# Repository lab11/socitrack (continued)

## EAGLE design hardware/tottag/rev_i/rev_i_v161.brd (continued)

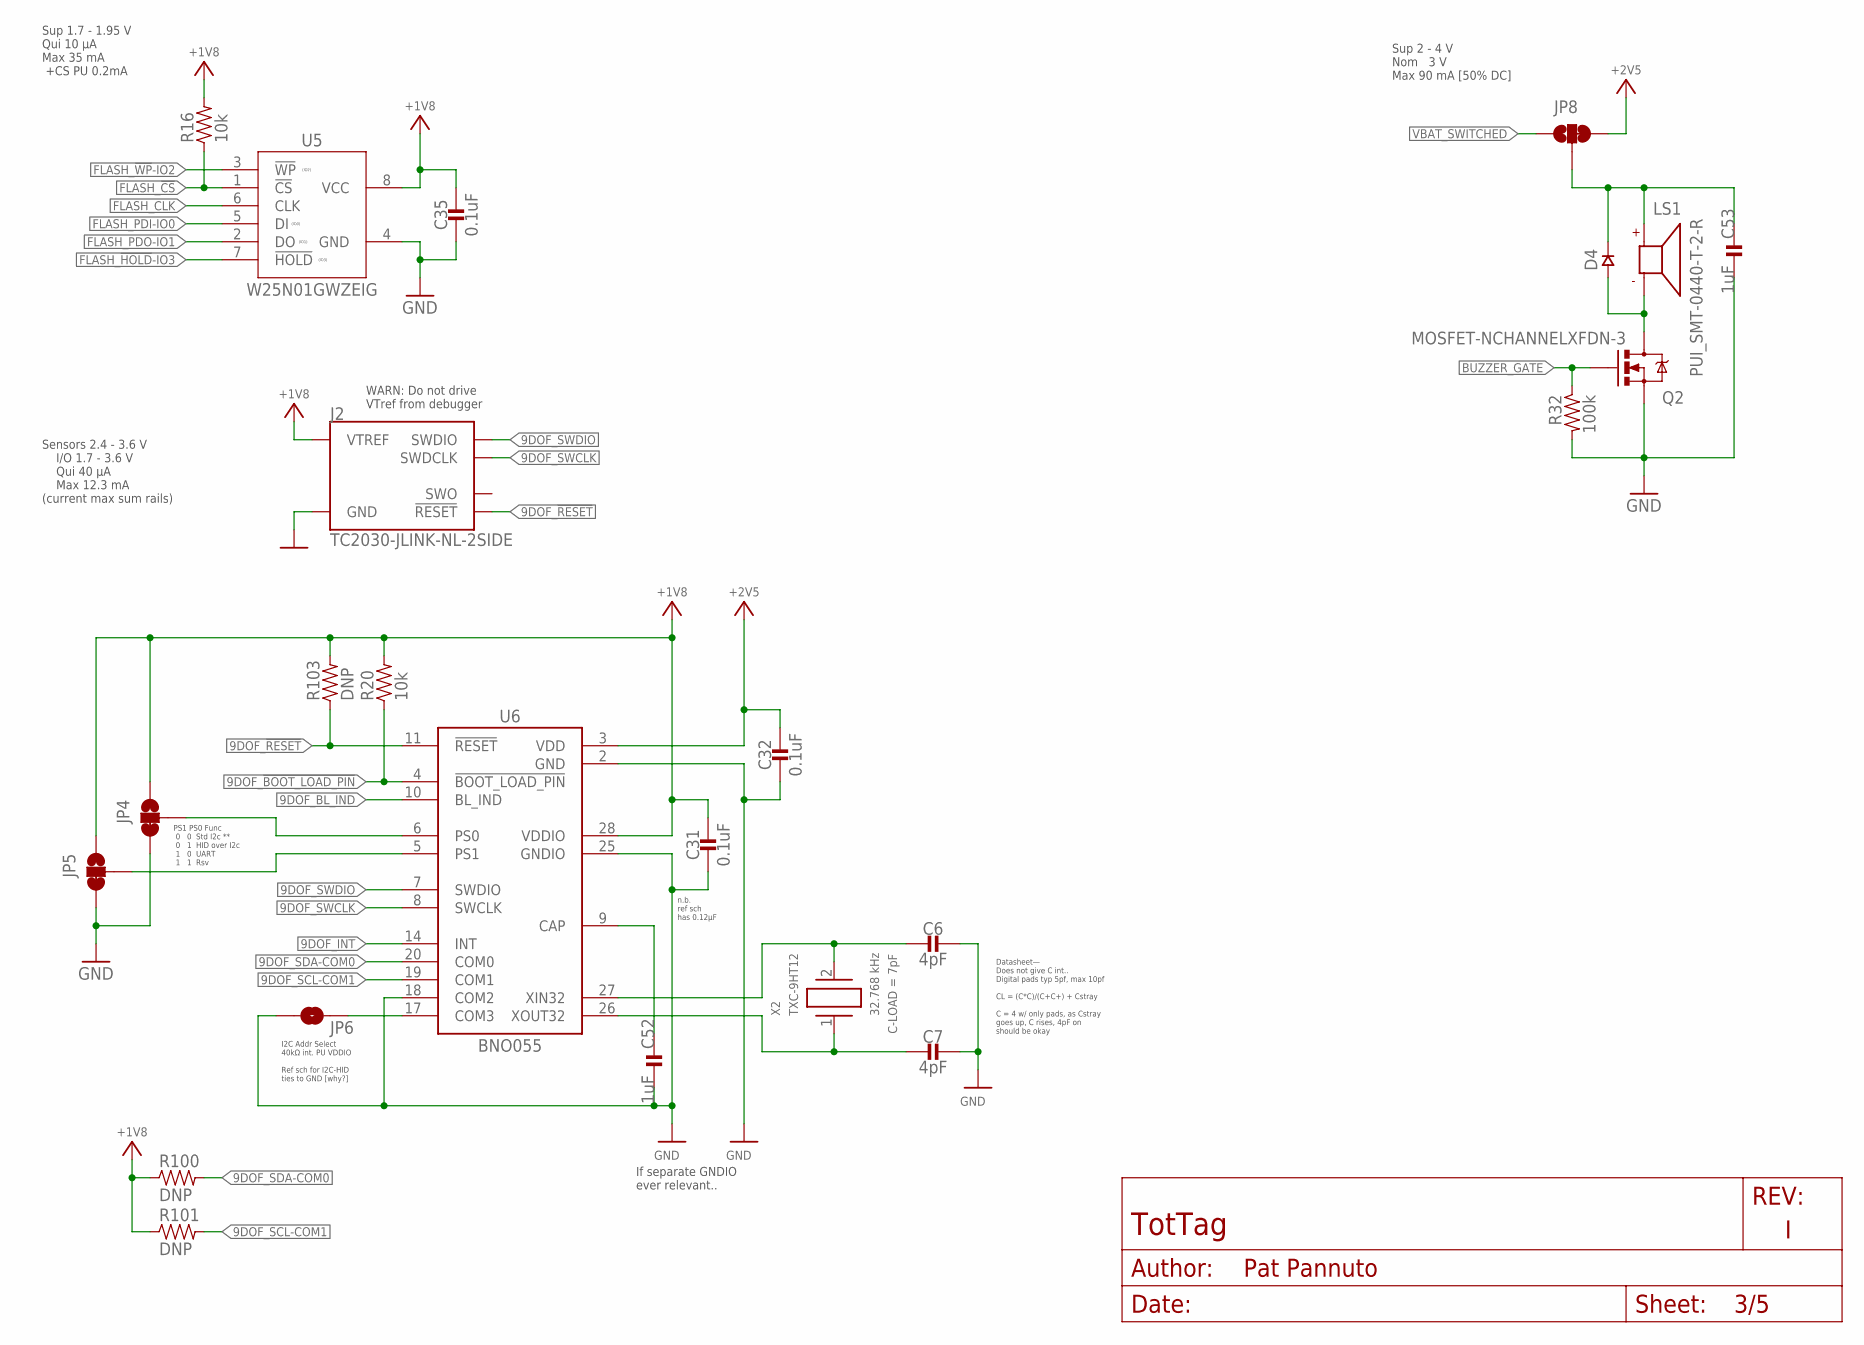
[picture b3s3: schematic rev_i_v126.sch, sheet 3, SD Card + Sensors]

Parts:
C6, C7: 4pF; 0201_CAP; MPN GRM0335C1H4R0BA01D
C31, C32, C35: 0.1uF; 0402_CAP; MPN CL05A104KP5NNNC
C52, C53: 1uF; 0201_CAP; MPN GRM033R61A105ME44D
D4: DIODE0402; 0402_DIODE; MPN CDSQR400B-HF; DIGIKEY 641-2087-1-ND
J2: TC2030-JLINK-NL-2SIDE; TC2030-IDC-NL-2SIDE
JP4, JP5, JP8: JUMPER-SMT_3_1-NC_TRACE_SILK; SMT-JUMPER_3_1-NC_TRACE_SILK
JP6: JUMPER-SMT_2_NO_SILK; SMT-JUMPER_2_NO_SILK
LS1: PUI_SMT-0440-T-2-R; SMT-0440-T-2-R
Q2: MOSFET-NCHANNELXFDN-3; XFDFN-3
R16, R20: 10k; 0402_RES; MPN RC0402JR-0710KL; DIGIKEY 311-10KJRCT-ND
R32: 100k; 0402_RES; MPN RT0402BRE07100KL
R100, R101, R103: DNP; 0603-RES
U5: W25N01GWZEIG; WSON127P800X600X80-9T430X340N
U6: BNO055; LGA28R0P510X4_5P2X3P8X1
X2: TXC-9HT12; MPN 9HT12-32.768KDZY-T

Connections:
9DOF_!BOOT_LOAD_PIN: R20.1, U6.4 (!BOOT_LOAD_PIN); also elsewhere on the board
9DOF_!RESET: J2.3 (!RESET), J2.B3 (!RESET), R103.1, U6.11 (!RESET); also elsewhere on the board
9DOF_BL_IND: U6.10 (BL_IND); also elsewhere on the board
9DOF_CAP: C52.P$1 (1), U6.9 (CAP)
9DOF_INT: U6.14 (INT); also elsewhere on the board
9DOF_SCL-COM1: R101.2, U6.19 (COM1); also elsewhere on the board
9DOF_SDA-COM0: R100.2, U6.20 (COM0); also elsewhere on the board
9DOF_SWCLK: J2.4 (SWDCLK), J2.B4 (SWDCLK), U6.8 (SWCLK)
9DOF_SWDIO: J2.2 (SWDIO), J2.B2 (SWDIO), U6.7 (SWDIO)
9DOF_XI: C6.P$2 (2), U6.27 (XIN32), X2.2
9DOF_XO: C7.P$2 (2), U6.26 (XOUT32), X2.1
+1V8: C31.1, C35.1, J2.1 (VTREF), J2.B1 (VTREF), JP4.1, JP5.1, R16.2, R20.2, R100.1, R101.1, R103.2, U5.8 (VCC), U6.28 (VDDIO); also elsewhere on the board
+2V5: C32.1, JP8.3, U6.3 (VDD); also elsewhere on the board
BUZZER_GATE: Q2.G, R32.1; also elsewhere on the board
BUZZER_SUPPLY: C53.P$1 (1), D4.CATHODE, JP8.2, LS1.+
FLASH_!CS: R16.1, U5.1 (!CS); also elsewhere on the board
FLASH_!HOLD!-IO3: U5.7 (!HOLD); also elsewhere on the board
FLASH_!WP!-IO2: U5.3 (!WP); also elsewhere on the board
FLASH_CLK: U5.6 (CLK); also elsewhere on the board
FLASH_PDI-IO0: U5.5 (DI); also elsewhere on the board
FLASH_PDO-IO1: U5.2 (DO); also elsewhere on the board
GND: C6.P$1 (1), C7.P$1 (1), C31.2, C32.2, C35.2, C52.P$2 (2), C53.P$2 (2), J2.5 (GND), J2.B5 (GND), JP4.3, JP5.3, JP6.1, Q2.S, R32.2, U5.4 (GND), U6.2 (GND), U6.18 (COM2), U6.25 (GNDIO); also elsewhere on the board
unnamed: D4.ANODE, LS1.- (N), Q2.D
unnamed: JP4.2, U6.6 (PS0)
unnamed: JP5.2, U6.5 (PS1)
unnamed: JP6.2, U6.17 (COM3)
VBAT_SWITCHED: JP8.1; also elsewhere on the board

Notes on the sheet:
Sup 1.7 - 1.95 V Qui 10 µA Max 35 mA +CS PU 0.2mA
Sensors 2.4 - 3.6 V I/O 1.7 - 3.6 V Qui 40 µA Max 12.3 mA (current max sum rails)
Sup 2 - 4 V Nom 3 V Max 90 mA [50% DC]
PS1 PS0 Func 0 0 Std I2c ** 0 1 HID over I2c 1 0 UART 1 1 Rsv
If separate GNDIO ever relevant..
I2C Addr Select 40kΩ int. PU VDDIO Ref sch for I2C-HID ties to GND [why?]
n.b. ref sch has 0.12µF
WARN: Do not drive VTref from debugger
Datasheet— Does not give C int.. Digital pads typ 5pf, max 10pf CL = (C*C)/(C+C+) + Cstray C = 4 w/ only pads, as Cstray goes up, C rises, 4pF on should be okay

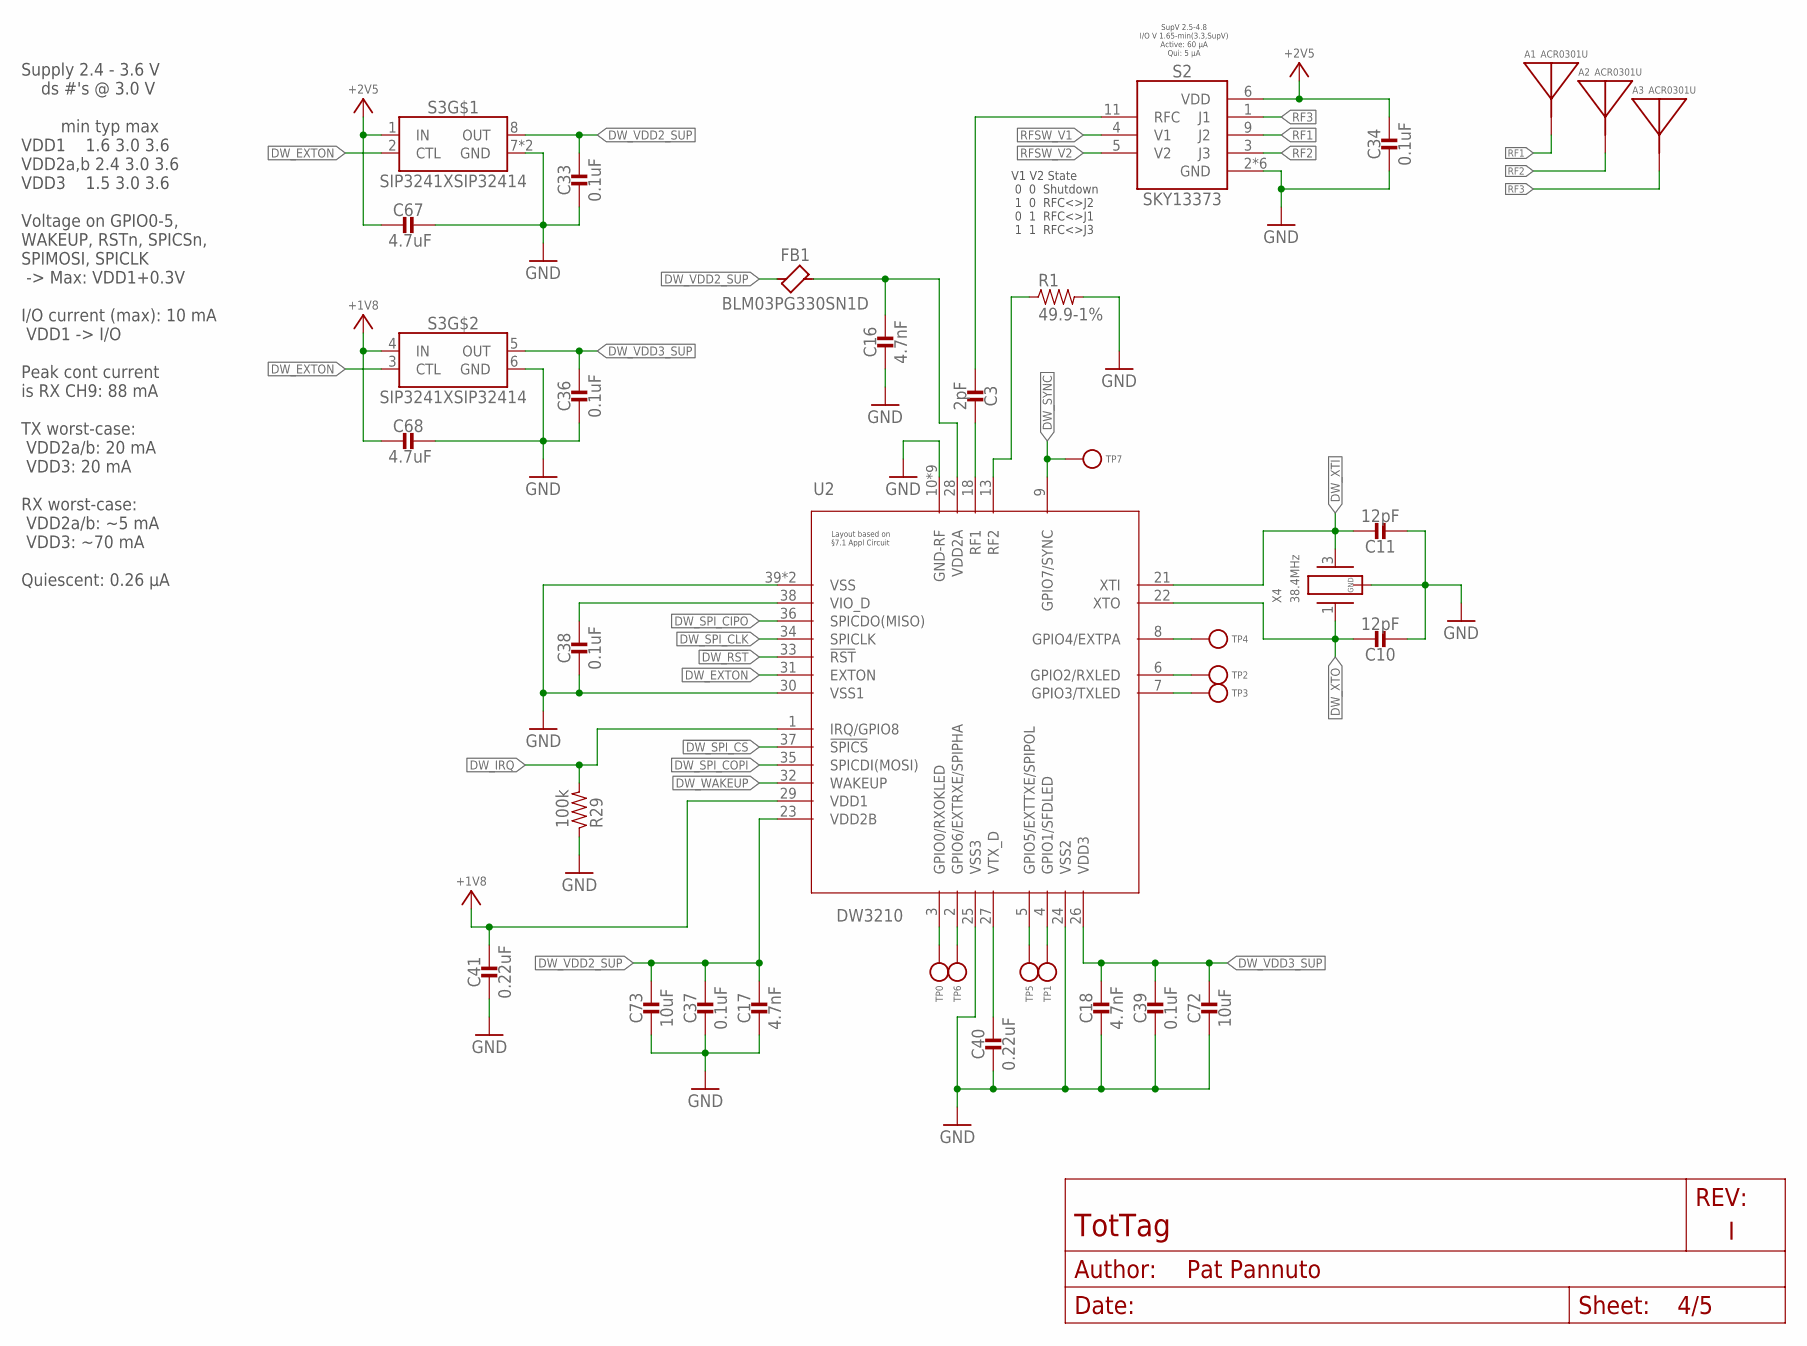
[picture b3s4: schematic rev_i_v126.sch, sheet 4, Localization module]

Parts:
A1, A2, A3: ACR0301U
C3: 2pF; 0201_CAP; MPN CBR02C209A5GAC
C10, C11: 12pF; 0402_CAP; MPN CBR04C120F5GAC; DIGIKEY 399-8815-2-ND
C16, C17, C18: 4.7nF; 0402_CAP; MPN C0402C472K3RAC7867
C33, C34, C36, C37, C38, C39: 0.1uF; 0402_CAP; MPN CL05A104KP5NNNC
C40, C41: 0.22uF; 0402_CAP; MPN CL05A224KP5NNNC
C67, C68: 4.7uF; 0402_CAP; MPN CL05A475MP5NRNC
C72, C73: 10uF; 0603_CAP; MPN CM105X5R106M25AT; DIGIKEY 1253-CM105X5R106M25ATCT-ND
FB1: BLM03PG330SN1D; 0201_FB; MPN BLM03PG330SN1D
R1: 49.9-1%; 0201_RES; MPN ERJ-1GNF49R9C
R29: 100k; 0402_RES; MPN RT0402BRE07100KL
S2: SKY13373
S3: SIP3241XSIP32414; TDFN2X2X0P6-8
TP0, TP1, TP2, TP3, TP4, TP5, TP6, TP7: TEST-POINT; PAD.03X.03
U2: DW3210; QFN40P500X500X80-40N
X4: 38.4MHz; FA-20H; MPN FA-20H 38.4000MF10Z-AS3; DIGIKEY SER3631CT-ND

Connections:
!DW_RST: U2.33 (!RST); also elsewhere on the board
!DW_SPI_CS: U2.37 (!SPICS); also elsewhere on the board
+1V8: C41.1, C68.2, S3.4 (IN), U2.29 (VDD1); also elsewhere on the board
+2V5: C34.1, C67.2, S2.6 (VDD), S3.1 (IN); also elsewhere on the board
DW_EXTON: S3.2 (CTL), S3.3 (CTL), U2.31 (EXTON)
DW_GPIO4: TP4.P$1, U2.8 (GPIO4/EXTPA)
DW_GPIO5: TP5.P$1, U2.5 (GPIO5/EXTTXE/SPIPOL)
DW_GPIO6: TP6.P$1, U2.2 (GPIO6/EXTRXE/SPIPHA)
DW_IRQ: R29.2, U2.1 (IRQ/GPIO8); also elsewhere on the board
DW_RF1: C3.P$1 (1), U2.18 (RF1)
DW_RF2: R1.1, U2.13 (RF2)
DW_RXLED: TP2.P$1, U2.6 (GPIO2/RXLED)
DW_RXOKLED: TP0.P$1, U2.3 (GPIO0/RXOKLED)
DW_SFDLED: TP1.P$1, U2.4 (GPIO1/SFDLED)
DW_SPI_CIPO: U2.36 (SPICDO(MISO)); also elsewhere on the board
DW_SPI_CLK: U2.34 (SPICLK); also elsewhere on the board
DW_SPI_COPI: U2.35 (SPICDI(MOSI)); also elsewhere on the board
DW_SYNC: TP7.P$1, U2.9 (GPIO7/SYNC)
DW_TXLED: TP3.P$1, U2.7 (GPIO3/TXLED)
DW_VDD2A: C16.1, FB1.P$2, U2.28 (VDD2A)
DW_VDD2_SUP: C17.1, C33.1, C37.1, C73.1, FB1.P$1, S3.8 (OUT), U2.23 (VDD2B)
DW_VDD3_SUP: C18.1, C36.1, C39.1, C72.1, S3.5 (OUT), U2.26 (VDD3)
DW_VIO_D: C38.1, U2.38 (VIO_D)
DW_VTX_D: C40.1, U2.27 (VTX_D)
DW_WAKEUP: U2.32 (WAKEUP); also elsewhere on the board
DW_XTI: C11.1, U2.21 (XTI), X4.3 (2)
DW_XTO: C10.1, U2.22 (XTO), X4.1
GND: C10.2, C11.2, C16.2, C17.2, C18.2, C33.2, C34.2, C36.2, C37.2, C38.2, C39.2, C40.2, C41.2, C67.1, C68.1, C72.2, C73.2, R1.2, R29.1, S2.2 (GND), S2.7 (GND), S2.8 (GND), S2.10 (GND), S2.12 (GND), S2.PAD (GND), S3.6 (GND), S3.7 (GND), S3.PAD (GND), U2.10 (GND-RF), U2.11 (GND-RF), U2.12 (GND-RF), U2.14 (GND-RF), U2.15 (GND-RF), U2.16 (GND-RF), U2.17 (GND-RF), U2.19 (GND-RF), U2.20 (GND-RF), U2.24 (VSS2), U2.25 (VSS3), U2.30 (VSS1), U2.39 (VSS), U2.40 (VSS), X4.2 (GND), X4.4 (GND); also elsewhere on the board
RF1: A1.FEED, S2.9 (J2)
RF2: A2.FEED, S2.3 (J3)
RF3: A3.FEED, S2.1 (J1)
RFC: C3.P$2 (2), S2.11 (RFC)
RFSW_V1: S2.4 (V1); also elsewhere on the board
RFSW_V2: S2.5 (V2); also elsewhere on the board

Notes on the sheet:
Supply 2.4 - 3.6 V ds #'s @ 3.0 V min typ max VDD1 1.6 3.0 3.6 VDD2a,b 2.4 3.0 3.6 VDD3 1.5 3.0 3.6 Voltage on GPIO0-5, WAKEUP, RSTn, SPICSn, SPIMOSI, SPICLK -> Max: VDD1+0.3V I/O current (max): 10 mA VDD1 -> I/O Peak cont current is RX CH9: 88 mA TX worst-case: VDD2a/b: 20 mA VDD3: 20 mA RX worst-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
SupV 2.5-4.8 I/O V 1.65-min(3.3,SupV) Active: 60 µA Qui: 5 µA
V1 V2 State 0 0 Shutdown 1 0 RFC<>J2 0 1 RFC<>J1 1 1 RFC<>J3

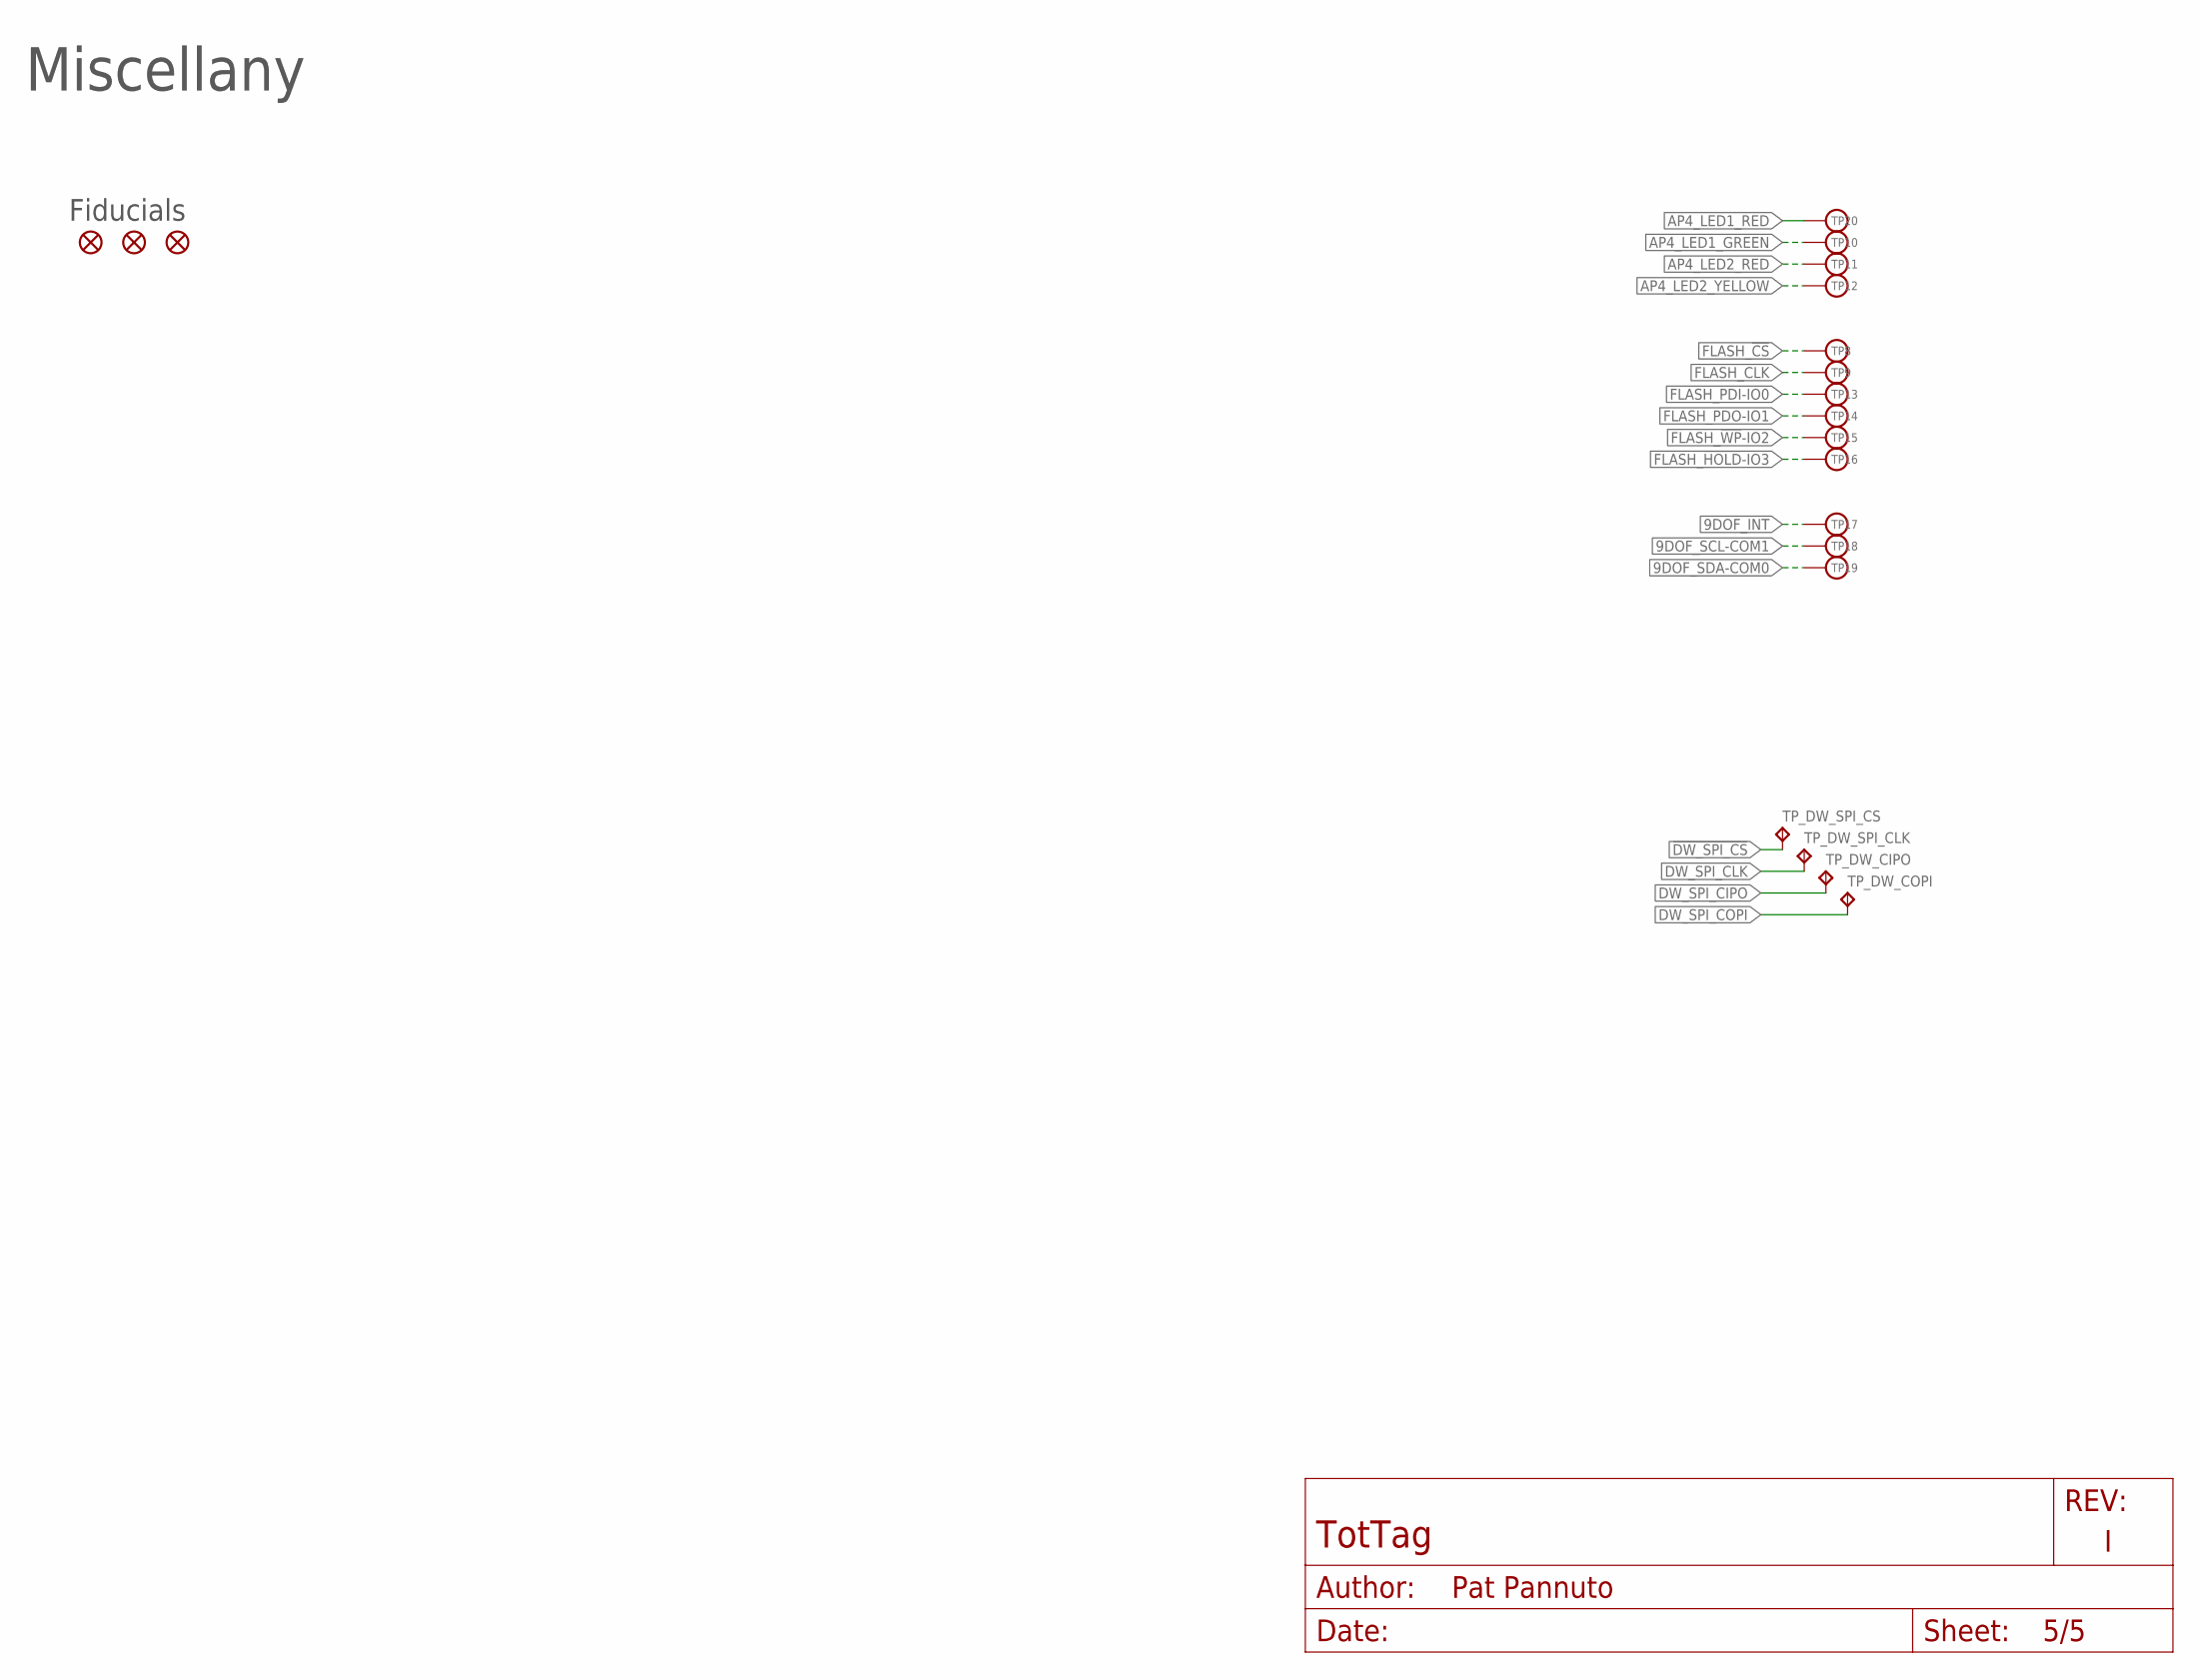
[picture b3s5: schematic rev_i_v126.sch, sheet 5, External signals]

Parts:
FD1, FD2, FD3: FIDUCIAL1X2; FIDUCIAL-1X2
TP8, TP9, TP10, TP11, TP12, TP13, TP14, TP15, TP16, TP17, TP18, TP19, TP20: TEST-POINT; PAD.03X.03
TP_DW_CIPO: TPTP06SQ; TP06SQ
TP_DW_COPI: TPTP06SQ; TP06SQ
TP_DW_SPI_CLK: TPTP06SQ; TP06SQ
TP_DW_SPI_CS: TPTP06SQ; TP06SQ

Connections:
9DOF_INT: TP17.P$1; also elsewhere on the board
9DOF_SCL-COM1: TP18.P$1; also elsewhere on the board
9DOF_SDA-COM0: TP19.P$1; also elsewhere on the board
!DW_SPI_CS: TP_DW_SPI_CS.TP; also elsewhere on the board
AP4_LED1_GREEN: TP10.P$1; also elsewhere on the board
AP4_LED1_RED: TP20.P$1; also elsewhere on the board
AP4_LED2_RED: TP11.P$1; also elsewhere on the board
AP4_LED2_YELLOW: TP12.P$1; also elsewhere on the board
DW_SPI_CIPO: TP_DW_CIPO.TP; also elsewhere on the board
DW_SPI_CLK: TP_DW_SPI_CLK.TP; also elsewhere on the board
DW_SPI_COPI: TP_DW_COPI.TP; also elsewhere on the board
FLASH_!CS: TP8.P$1; also elsewhere on the board
FLASH_!HOLD!-IO3: TP16.P$1; also elsewhere on the board
FLASH_!WP!-IO2: TP15.P$1; also elsewhere on the board
FLASH_CLK: TP9.P$1; also elsewhere on the board
FLASH_PDI-IO0: TP13.P$1; also elsewhere on the board
FLASH_PDO-IO1: TP14.P$1; also elsewhere on the board

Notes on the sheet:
Miscellany
Fiducials

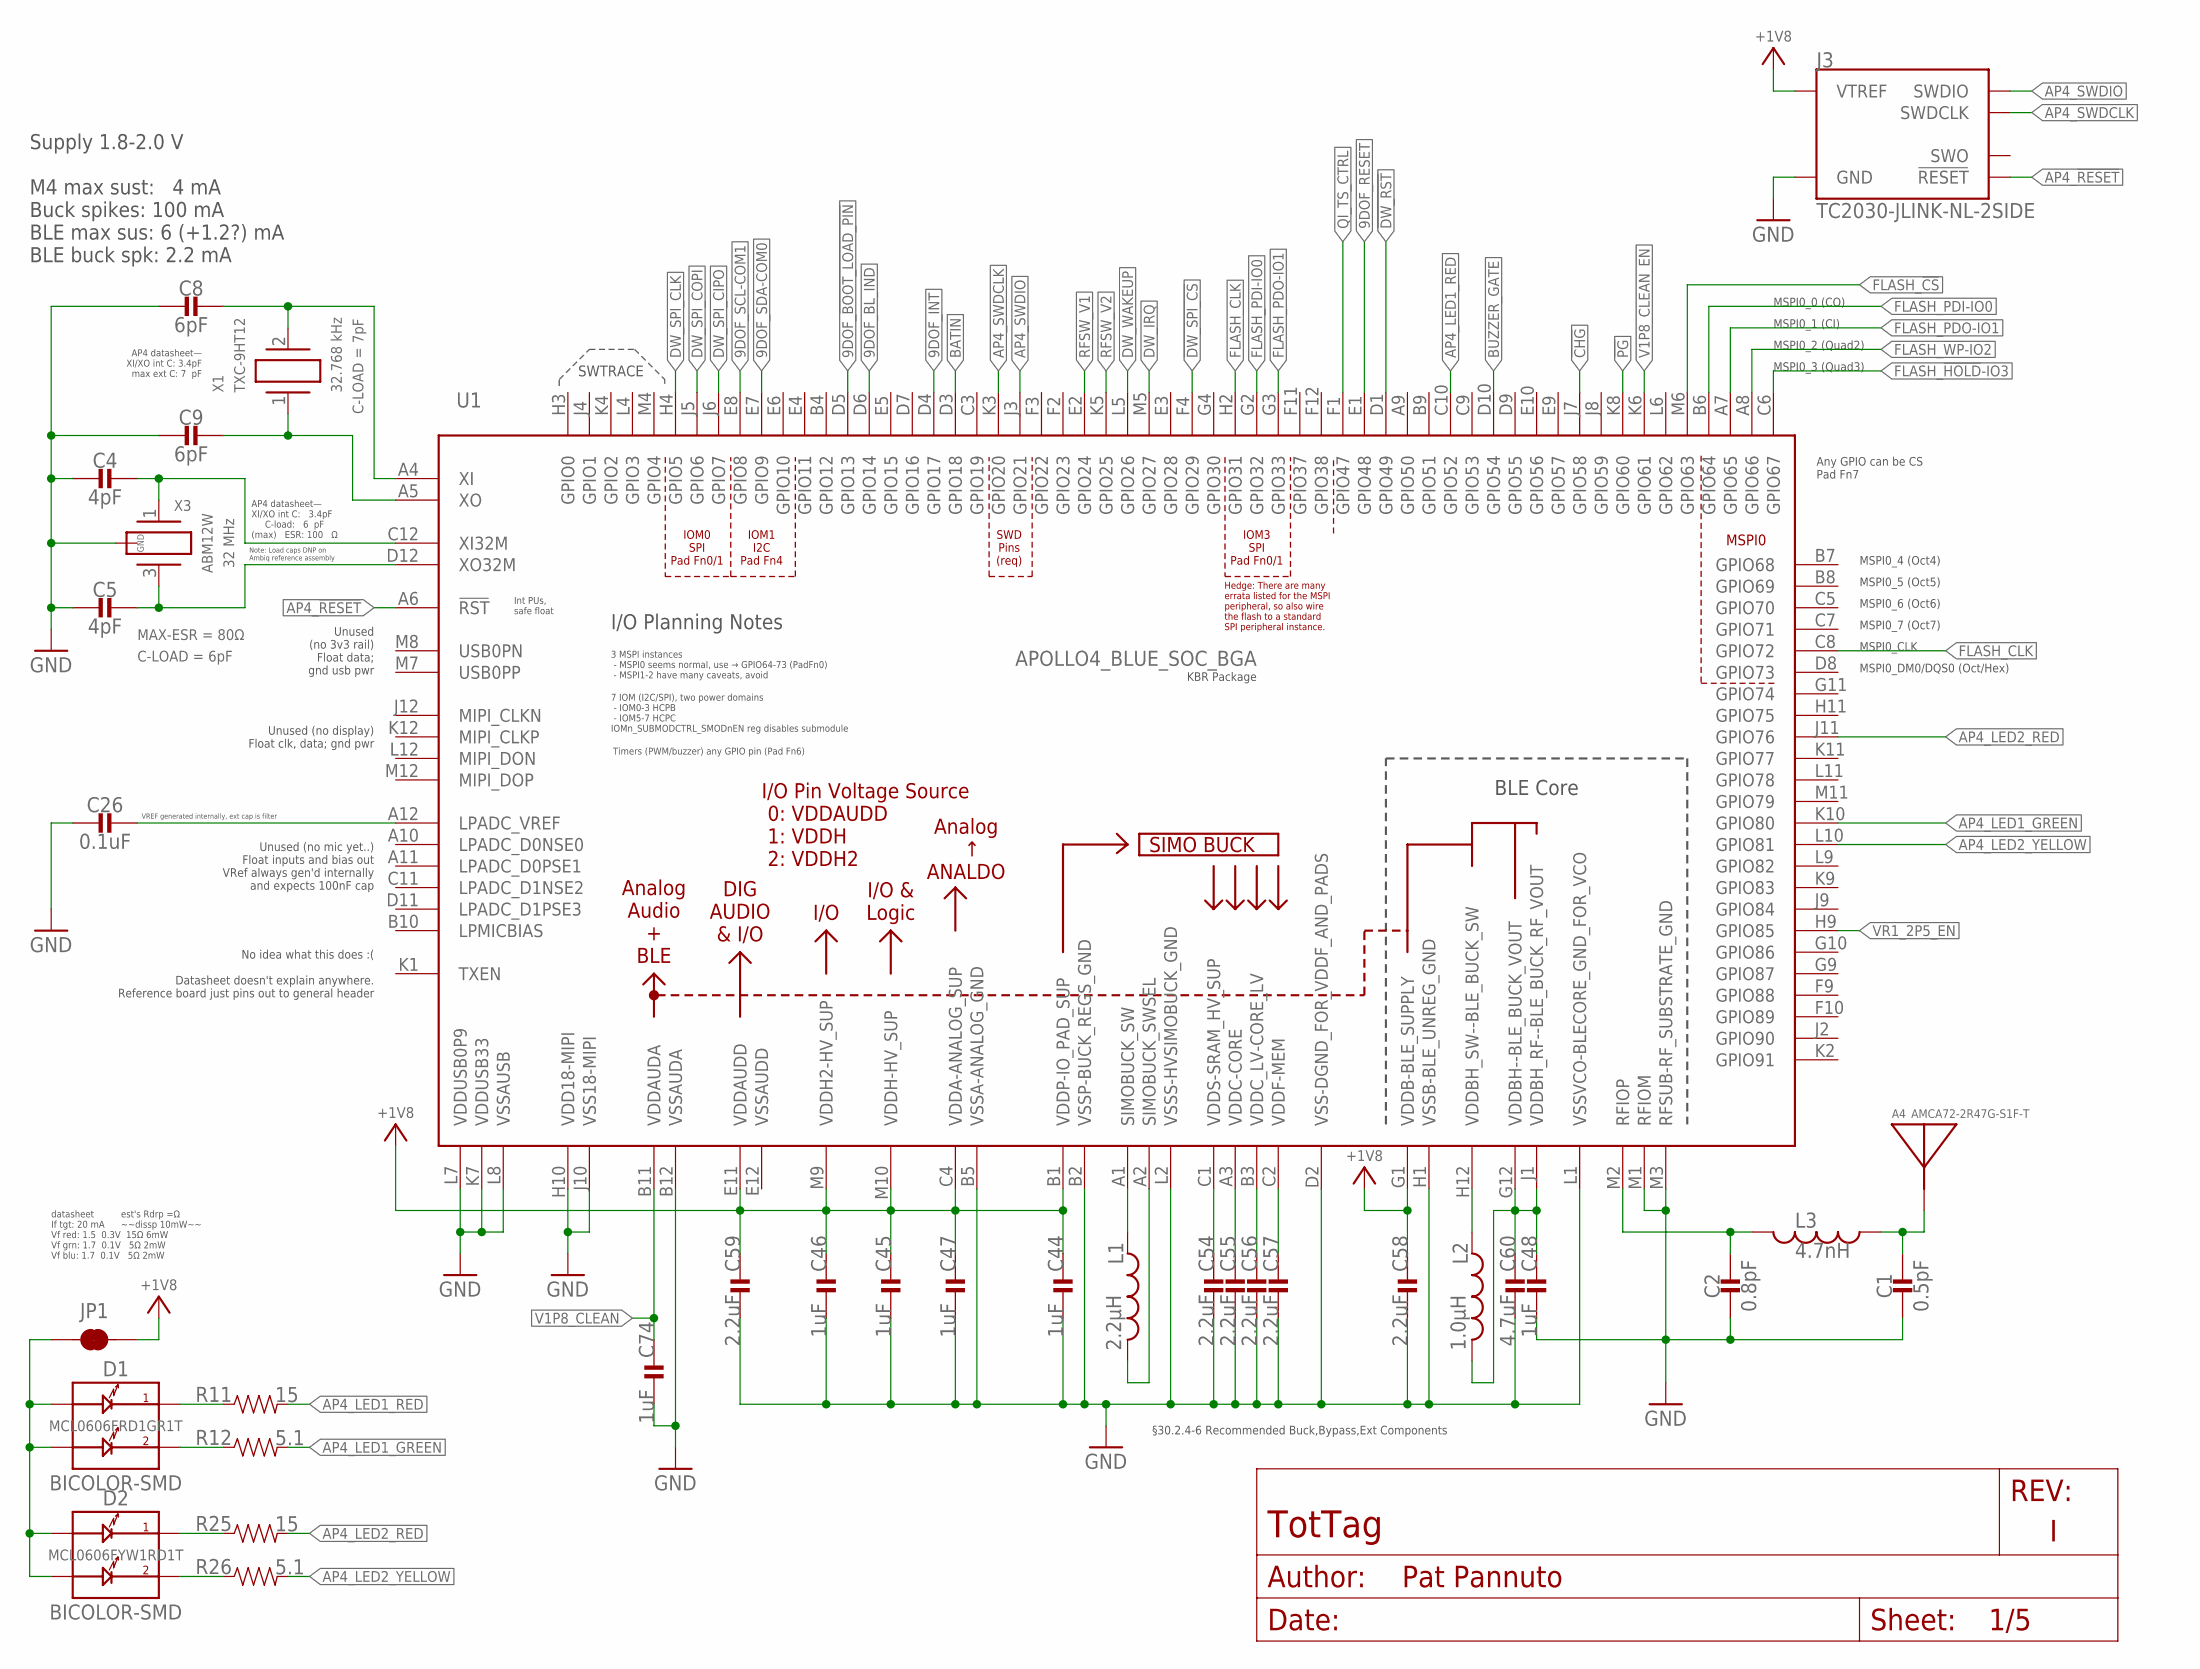
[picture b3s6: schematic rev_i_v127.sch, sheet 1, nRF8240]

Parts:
A4: AMCA72-2R47G-S1F-T; AMCA72-2R470G-S1F-T
C1: 0.5pF; 0402_CAP; MPN GJM1555C1HR50WB01D
C2: 0.8pF; 0402_CAP; MPN GJM1555C1HR80WB01D
C4, C5: 4pF; 0201_CAP; MPN GRM0335C1H4R0BA01D
C8, C9: 6pF; 0201_CAP; MPN GRM0335C1H6R0BA01D
C26: 0.1uF; 0201_CAP; MPN CL05A104KP5NNNC
C44, C45, C46, C47, C48, C74: 1uF; 0201_CAP; MPN GRM033R61A105ME44D
C54, C55, C56, C57, C58, C59: 2.2uF; 0201_CAP; MPN GRM033R61A225KE47D
C60: 4.7uF; 0402_CAP; MPN CL05A475MP5NRNC
D1: BICOLOR-SMD; LED-0606; MPN MCL0606FRD1GR1T
D2: BICOLOR-SMD; LED-0606; MPN MCL0606FYW1RD1T
J3: TC2030-JLINK-NL-2SIDE; TC2030-IDC-NL-2SIDE
JP1: JUMPER-SMT_2_NC_TRACE_SILK; SMT-JUMPER_2_NC_TRACE_SILK
L1: 2.2µH; 0805_CAP; MPN DFE201210U-2R2M=P2
L2: 1.0µH; 0603_CAP; MPN DFE18SAN1R0ME0L
L3: 4.7nH; 0402_CAP; MPN LQW15AN4N7G8ZD
R11, R25: 15; 0402_RES; MPN RC0402JR-0715RL
R12, R26: 5.1; 0402_RES; MPN RC0402JR-075R1L
U1: APOLLO4_BLUE_SOC_BGA
X1: TXC-9HT12; MPN 9HT12-32.768KDZY-T
X3: ABM12W; MPN ABM12W-32.0000MHZ-6-D1X-T3

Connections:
9DOF_!BOOT_LOAD_PIN: U1.D5 (GPIO13); also elsewhere on the board
9DOF_!RESET: U1.E1 (GPIO48); also elsewhere on the board
9DOF_BL_IND: U1.D6 (GPIO14); also elsewhere on the board
9DOF_INT: U1.D4 (GPIO17); also elsewhere on the board
9DOF_SCL-COM1: U1.E8 (GPIO8); also elsewhere on the board
9DOF_SDA-COM0: U1.E7 (GPIO9); also elsewhere on the board
!CHG: U1.J7 (GPIO58); also elsewhere on the board
!DW_RST: U1.D1 (GPIO49); also elsewhere on the board
!DW_SPI_CS: U1.F4 (GPIO29); also elsewhere on the board
!PG: U1.K8 (GPIO60); also elsewhere on the board
+1V8: C44.P$1 (1), C45.P$1 (1), C46.P$1 (1), C47.P$1 (1), C58.P$1 (1), C59.P$1 (1), J3.1 (VTREF), J3.B1 (VTREF), JP1.2, U1.B1 (VDDP-IO_PAD_SUP), U1.C4 (VDDA-ANALOG_SUP), U1.E11 (VDDAUDD), U1.G1 (VDDB-BLE_SUPPLY), U1.M9 (VDDH2-HV_SUP), U1.M10 (VDDH-HV_SUP); also elsewhere on the board
AP4_!RESET: J3.3 (!RESET), J3.B3 (!RESET), U1.A6 (!RST)
AP4_LED1_GREEN: R12.2, U1.K10 (GPIO80); also elsewhere on the board
AP4_LED1_RED: R11.2, U1.C10 (GPIO52); also elsewhere on the board
AP4_LED2_BLUE_COMM: D1.1-C1 (C1), R11.1
AP4_LED2_RED: R25.2, U1.J11 (GPIO76); also elsewhere on the board
AP4_LED2_YELLOW: R26.2, U1.L10 (GPIO81); also elsewhere on the board
AP4_LED_BLUE_COMM: D2.2-C2 (C2), R26.1
AP4_LED_GREEN_COMM: D2.1-C1 (C1), R25.1
AP4_LED_RED_COMM: D1.2-C2 (C2), R12.1
AP4_LPADC_VREF: C26.P$1 (1), U1.A12 (LPADC_VREF)
AP4_RFIOP: C2.1, L3.2, U1.M2 (RFIOP)
AP4_SWDCLK: J3.4 (SWDCLK), J3.B4 (SWDCLK), U1.K3 (GPIO20)
AP4_SWDIO: J3.2 (SWDIO), J3.B2 (SWDIO), U1.J3 (GPIO21)
AP4_VDDBH: C48.P$1 (1), C60.1, L2.2, U1.G12 (VDDBH--BLE_BUCK_VOUT), U1.J1 (VDDBH_RF--BLE_BUCK_RF_VOUT)
AP4_VDDBH_SW: L2.1, U1.H12 (VDDBH_SW--BLE_BUCK_SW)
AP4_VDDC: C55.P$1 (1), U1.A3 (VDDC-CORE)
AP4_VDDC_LV: C56.P$1 (1), U1.B3 (VDDC_LV-CORE_LV)
AP4_VDDF: C57.P$1 (1), U1.C2 (VDDF-MEM)
AP4_VDDS: C54.P$1 (1), U1.C1 (VDDS-SRAM_HV_SUP)
AP4_XI: C8.P$1 (1), U1.A4 (XI), X1.2
AP4_XI32M: C4.P$1 (1), U1.C12 (XI32M), X3.1
AP4_XO: C9.P$1 (1), U1.A5 (XO), X1.1
AP4_XO32M: C5.P$1 (1), U1.D12 (XO32M), X3.3 (2)
BATIN: U1.D3 (GPIO18); also elsewhere on the board
BLE_ANT_FEED: A4.S1, C1.1, L3.1
BUZZER_GATE: U1.D10 (GPIO54); also elsewhere on the board
DW_IRQ: U1.M5 (GPIO27); also elsewhere on the board
DW_SPI_CIPO: U1.J6 (GPIO7); also elsewhere on the board
DW_SPI_CLK: U1.H4 (GPIO5); also elsewhere on the board
DW_SPI_COPI: U1.J5 (GPIO6); also elsewhere on the board
DW_WAKEUP: U1.L5 (GPIO26); also elsewhere on the board
FLASH_!CS: U1.M6 (GPIO63); also elsewhere on the board
FLASH_!HOLD!-IO3: U1.C6 (GPIO67); also elsewhere on the board
FLASH_!WP!-IO2: U1.A8 (GPIO66); also elsewhere on the board
FLASH_CLK: U1.C8 (GPIO72), U1.H2 (GPIO31); also elsewhere on the board
FLASH_PDI-IO0: U1.B6 (GPIO64), U1.G2 (GPIO32); also elsewhere on the board
FLASH_PDO-IO1: U1.A7 (GPIO65), U1.G3 (GPIO33); also elsewhere on the board
GND: C1.2, C2.2, C4.P$2 (2), C5.P$2 (2), C8.P$2 (2), C9.P$2 (2), C26.P$2 (2), C44.P$2 (2), C45.P$2 (2), C46.P$2 (2), C47.P$2 (2), C48.P$2 (2), C54.P$2 (2), C55.P$2 (2), C56.P$2 (2), C57.P$2 (2), C58.P$2 (2), C59.P$2 (2), C60.2, C74.P$2 (2), J3.5 (GND), J3.B5 (GND), U1.B2 (VSSP-BUCK_REGS_GND), U1.B5 (VSSA-ANALOG_GND), U1.B12 (VSSAUDA), U1.D2 (VSS-DGND_FOR_VDDF_AND_PADS), U1.H1 (VSSB-BLE_UNREG_GND), U1.H10 (VDD18-MIPI), U1.J10 (VSS18-MIPI), U1.K7 (VDDUSB33), U1.L1 (VSSVCO-BLECORE_GND_FOR_VCO), U1.L2 (VSSS-HVSIMOBUCK_GND), U1.L7 (VDDUSB0P9), U1.L8 (VSSAUSB), U1.M1 (RFIOM), U1.M3 (RFSUB-RF_SUBSTRATE_GND), X3.2 (GND), X3.4 (GND); also elsewhere on the board
LED_SUP: D1.3-A1 (A1), D1.4-A2 (A2), D2.3-A1 (A1), D2.4-A2 (A2), JP1.1
unnamed: L1.P$1 (1), U1.A1 (SIMOBUCK_SW)
unnamed: L1.P$2 (2), U1.A2 (SIMOBUCK_SWSEL)
QI_TS_CTRL: U1.F1 (GPIO47); also elsewhere on the board
RFSW_V1: U1.E2 (GPIO24); also elsewhere on the board
RFSW_V2: U1.K5 (GPIO25); also elsewhere on the board
V1P8_CLEAN: C74.P$1 (1), U1.B11 (VDDAUDA); also elsewhere on the board
V1P8_CLEAN_EN: U1.K6 (GPIO61); also elsewhere on the board
VR1_2P5_EN: U1.H9 (GPIO85); also elsewhere on the board

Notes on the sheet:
Supply 1.8-2.0 V M4 max sust: 4 mA Buck spikes: 100 mA BLE max sus: 6 (+1.2?) mA BLE buck spk: 2.2 mA
Note: Load caps DNP on Ambiq reference assembly
Int PUs, safe float
Unused (no 3v3 rail) Float data; gnd usb pwr
Unused (no display) Float clk, data; gnd pwr
Unused (no mic yet..) Float inputs and bias out VRef always gen'd internally and expects 100nF cap
No idea what this does :( Datasheet doesn't explain anywhere. Reference board just pins out to general header
I/O Planning Notes
3 MSPI instances - MSPI0 seems normal, use → GPIO64-73 (PadFn0) - MSPI1-2 have many caveats, avoid
7 IOM (I2C/SPI), two power domains - IOM0-3 HCPB - IOM5-7 HCPC IOMn_SUBMODCTRL_SMODnEN reg disables submodule
MSPI0
IOM0 SPI Pad Fn0/1
IOM1 I2C Pad Fn4
Timers (PWM/buzzer) any GPIO pin (Pad Fn6)
MSPI0_1 (CI)
MSPI0_0 (CO)
MSPI0_7 (Oct7)
MSPI0_6 (Oct6)
MSPI0_5 (Oct5)
MSPI0_4 (Oct4)
MSPI0_3 (Quad3)
MSPI0_2 (Quad2)
MSPI0_CLK
MSPI0_DM0/DQS0 (Oct/Hex)
KBR Package
Any GPIO can be CS Pad Fn7
datasheet est's Rdrp =Ω If tgt: 20 mA ~~dissp 10mW~~ Vf red: 1.5 0.3V 15Ω 6mW Vf grn: 1.7 0.1V 5Ω 2mW Vf blu: 1.7 0.1V 5Ω 2mW
§30.2.4-6 Recommended Buck,Bypass,Ext Components
SWTRACE
SWD Pins (req)
VREF generated internally, ext cap is filter
IOM3 SPI Pad Fn0/1
Hedge: There are many errata listed for the MSPI peripheral, so also wire the flash to a standard SPI peripheral instance.
AP4 datasheet— XI/XO int C: 3.4pF max ext C: 7 pF
AP4 datasheet— XI/XO int C: 3.4pF C-load: 6 pF (max) ESR: 100 Ω
